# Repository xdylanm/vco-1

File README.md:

# vco-1
Sawtooth core VCO based on Moritz Klein's DIY VCO. 

The general design and test description can be found on Moritz Klein's channel. The oscillator core is a ramp generator driven by a Schmitt trigger inverter and capacitor, controlled by an NPN. 

## Notes

* Using 2N3904 (NPN) and 2N3906 (PNP)
* Implemented a different triangle wave generator based on a precision rectifier circuit. The triangle generator sums a buffered ramp and an inverted, rectified ramp with balancing incorporated with a trimmer on the rectifier sum input.
* Made the coarse adjust an internal trimmer: "factory" tuning involves adjusting the coarse bias on the PNP base with both the coarse level adjust (high side) and divider scaling (low side). Might as well get that set on the bench then fine tune in operation.
* Option to configure the pulse output as a non-inverting summer (from Synth Mages) rather than open loop comparator.
* There are other variants without the Schmitt trigger inverter (e.g. hyestersis in another op-amp). There is also a 12V tolerant single Schmitt trigger inverter (TC4S584F) as an option for a future SMT version. 

## Oscillator Core Theory of Operation

The core of the oscillator is composed of the capacitor C1 and NPN BJT Q1. C1 is charged by the Schmitt trigger inverter U1A through D1 and discharged by Q1. Adjusting the bias on the base of Q1 adjusts the discharge rate of C1. 

The hysteresis on the CD40106 inverter is approximately 3V for a 12V supply (measured 2.8V on the bench). Assuming tuning over six octaves from 16Hz (~$C_0$ ) to 1024Hz (~$C_6$), the discharge time should range from approximately 1ms to 100ms. Using a 2.2nF capacitor for C1, the range of collector currents in Q1 is
$$
I_C \sim C\frac{dV}{dt} \to \left\{\begin{array}{ll}66nA & t_{discharge}=100ms \\ 6.6\mu A & t_{discharge}=1ms\end{array}\right.
$$
The basic model for the collector current is
$$
I_C = I_S \left(e^{\frac{V_{BE}}{V_T}} - 1\right)\to V_{BE}=V_T \ln\left(\frac{I_C}{I_S}+1\right)\simeq V_T(\ln I_C-\ln I_S)
$$
Assuming $I_S=10^{-13}A$, $V_{BE}$ ranges from 350mV to 470mV  ($V_T=26mV$). For larger $I_S$ , the low end of the range for $V_{BE}$ will be reduced (e.g. 290mV for $I_S=10^{-12}A$ ). The span of the range remains constant.

PNP BJT Q2 acts as a buffer in an emitter-follower configuration and counteracts the thermal response of Q1. Since the base voltage of Q1 should be below saturation (approximately 0.4V), there is an 11V drop across R1, which results in a bias current of approximately $11\mu A$ into the emitter and $V_{EB}\sim 0.5V$ for Q2. 

The  CV input is designed for a range between 0 and 5V (V/oct). $V_{BE}$ should vary by 90-120mV, which corresponds to a scaling of 0.018 to 0.024. The resistor divider formed by R6+TH1 and R5+RV1 creates this scaling: R6+TH1 is 110k such that R5+RV1 should range between 2k and 2.6k (R5=1.5k and RV1 ranges from 0 to 2k).

**Tuning Note:** Use an input that varies by 1V (e.g. alternate between 1V and 2V). If the difference in frequency between the same note in adjacent octaves is less than a factor of 2, increase RV1 to increase the gain of the resistor divider.

To set the low end of the range, the network including R19, R20, and RV3 is used to set a bias voltage. This is summed with the CV input through R7+TH3. As with the CV input, R7+TH3 creates a resistor divider with R5+RV1, which determines the gain applied to the bias voltage. Since $V_{EB}$ of Q2 is $\sim 0.5V$ and the low end of the range for $V_B$ of Q1 is 250-350mV, the base of Q2 is biased between -250mV and -150mV (more range here is better depending on the transistor characteristics - the tradeoff is tuning sensitivity). A factor of 40 reduces -12V to -300mV. R19 will limit the low end of the range and R20 will limit the high end. 

**Ideal Tuning**

* Assume $f_{C_0}=16Hz$ is the low frequency reference such that $t_{discharge,0} = 62.5ms$. 

* Use $\Delta V$ from the inverter hysteresis ($\Delta V = 3V$) and C1=2.2nF to obtain 
  $$
  I_{C,0} = C \frac{dV}{dt} = C \Delta V f_{C_0} = 2.2\cdot 10^{-9} \cdot 3 \cdot 16 = 106\mathrm{nA}
  $$

* Determine $V_{BE,0}$ and $\Delta V_{BE}$ , where $V_{BE}$ is the bias voltage to establish current $I_{C,0}$ through the NPN and $\Delta V_{BE}$ is the change in $V_{BE}$ to double the current,  
  $$
  \begin{align*}
  \Delta V_{BE} &\equiv nV_T \ln 2I_{C} - nV_T\ln I_C = nV_T \ln 2 \\
  V_{BE,0} &\equiv nV_T\left(\ln I_{C,0} - \ln I_{S}\right)
  \end{align*}
  $$

* Adjust the gain of the voltage divider (RV1) such that a change of 1V results in a doubling of the current $I_C$ (set $\Delta V_{BE} \approx 18\mathrm{mV}$).

* Adjust the offset with the coarse tuning pot such that the base of the NPN is biased to $V_{BE,0}$ when the input CV is 0V. 

## Assembly and Test

### 1. Power

* Populate the power input and filtering components at the bus connector. Verify the orientation of the polarity protection diodes D2 and D3.
* Connect the board to power and verify voltage levels.

### 2. Oscillator Core, Saw and Pulse Outputs

* Populate the input network (coarse adjust, fine adjust, CV and FM). Note that the board-edge pots (RV2 and RV6) must have their leads trimmed flush with the bottom of the board so that the mono jacks mount flush. Install the pots first and jacks later.
* Populate the transistors Q1 and Q2, socket and 40106 inverter (U1), diode D1 and capacitor C1.
* Populate the socket and TL074 op amp (U2) and the components for the pulse and saw outputs. This is required to generated a buffered signal from the oscillator core at TP9 (or after the DC block at TP3)
* Tune the oscillator (16Hz for a 0V input on CV, 32Hz for 1V, etc.) by adjusting RV1 and RV3. RV1 sets the gain of the voltage divider and should be adjust such that a 1V difference results in a frequency doubling. Next, adjust RV3 to set the base frequency. There is some coupling between the resistive networks, so iteration is required.
* Check the levels for the Saw and Pulse outputs (confirm ~10Vpp). Check the PWM adjustment and confirm a full range of pulse widths.

### 3. Triangle Output

* Populate the discrete components (watch the orientation on diodes D4 and D5) and the socket and TL074 op amp (U3). Populate the last jack.
* Power on the board and check the Triangle output. Adjust RV7 to balance the triangle (it won't be perfect at all frequencies; there is a short spike at the transition).

## Changes

#### V1.1.20240726

* Added additional test points, fixed test point pad to fit standard 0.1" header pins
* R14 to 82k (not tested; pulse out Vpp measured at 8.5V with 68k)
* Added C13 to remove spike in saw output
* R26 to 68k to fix level for triangle output range (now 9.6Vpp)

#### V1.0.20240714

Original PCB

## References

1. Moritz Klein: [DIY VCO Series](https://youtube.com/playlist?list=PLHeL0JWdJLvTuGCyC3qvx0RM39YvopVQN&si=mLFLNtdBjMHdq1OI)
2. Precision rectifier circuit: [Circuit Digest](https://circuitdigest.com/electronic-circuits/half-wave-and-full-wave-precision-rectifier-circuit-using-op-amp)
3. Synth Mages: [DIY VCO variant](https://gitea.circuitlocution.com/synth_mages/MK_VCO)

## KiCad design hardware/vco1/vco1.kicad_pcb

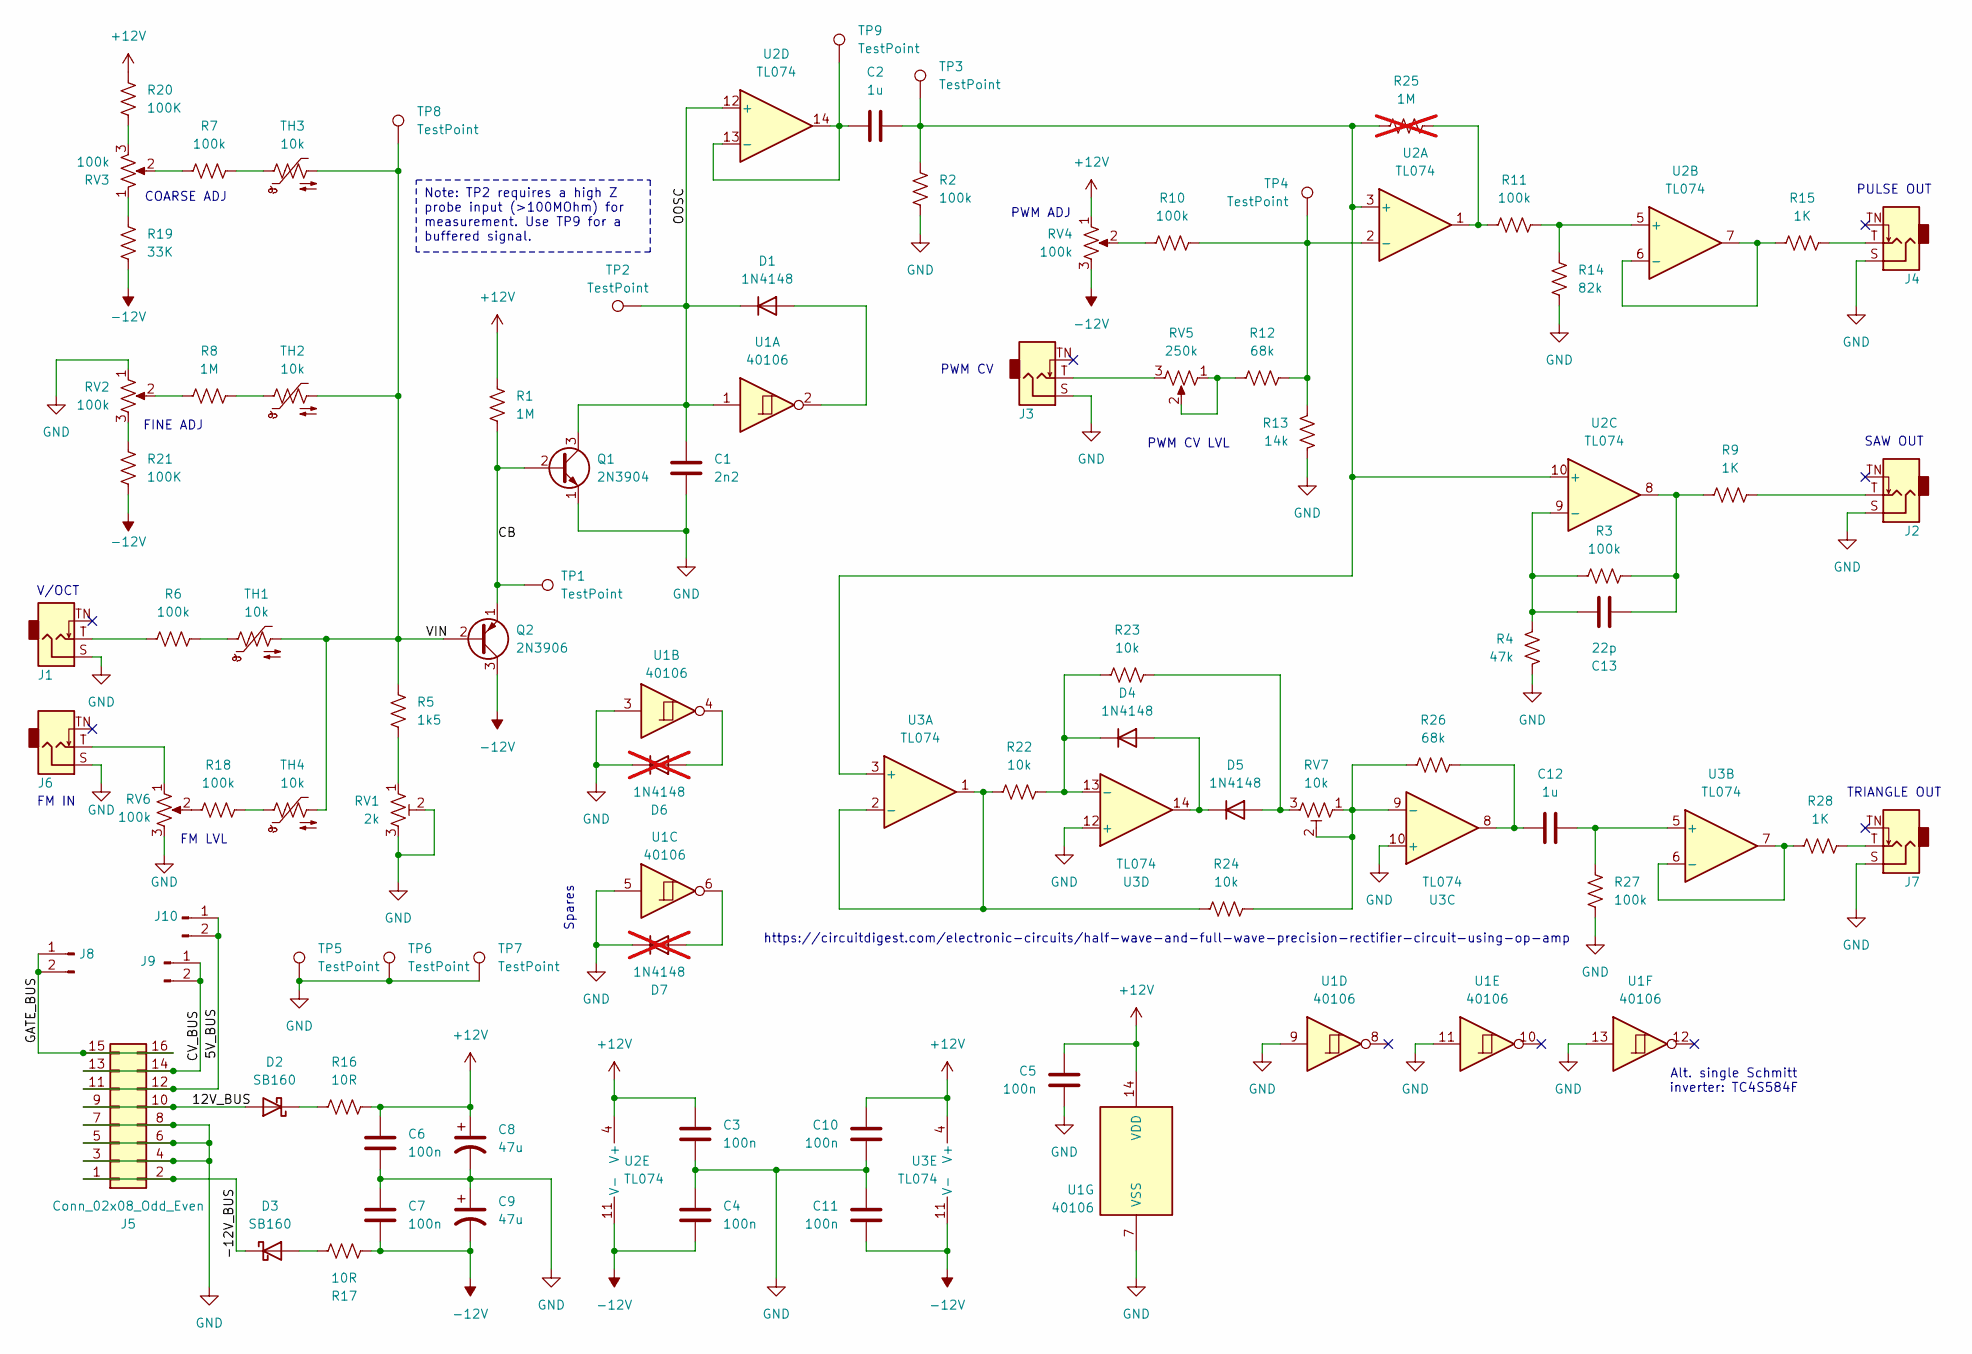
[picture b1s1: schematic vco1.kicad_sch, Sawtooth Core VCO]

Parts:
C1: 2n2; C_Rect_L7.2mm_W2.5mm_P5.00mm_FKS2_FKP2_MKS2_MKP2
C2, C12: 1u; C_Disc_D5.0mm_W2.5mm_P5.00mm
C3, C4, C5, C6, C7, C10, C11: 100n; C_Disc_D5.0mm_W2.5mm_P5.00mm
C8, C9: 47u; CP_Radial_D5.0mm_P2.50mm
C13: 22p; C_Disc_D5.0mm_W2.5mm_P5.00mm
D1, D4, D5: 1N4148; D_DO-35_SOD27_P2.54mm_Vertical_KathodeUp
D2, D3: SB160; D_DO-41_SOD81_P10.16mm_Horizontal
D6, D7: 1N4148; D_DO-35_SOD27_P2.54mm_Vertical_KathodeUp; not fitted
J1, J2, J3, J4, J6, J7: AudioJack2_SwitchT; CONN_MJ-3502
J5: Conn_02x08_Odd_Even; IDC-Header_2x08_P2.54mm_Vertical
J8, J9, J10: Conn_01x02_Pin; PinHeader_1x02_P2.54mm_Vertical
Q1: 2N3904; TO-92_Inline_Wide
Q2: 2N3906; TO-92_Inline_Wide
R1: 1M; R_Axial_DIN0207_L6.3mm_D2.5mm_P7.62mm_Horizontal
R2, R3, R6, R7, R10, R18, R27: 100k; R_Axial_DIN0204_L3.6mm_D1.6mm_P2.54mm_Vertical
R4: 47k; R_Axial_DIN0204_L3.6mm_D1.6mm_P2.54mm_Vertical
R5: 1k5; R_Axial_DIN0204_L3.6mm_D1.6mm_P2.54mm_Vertical
R8: 1M; R_Axial_DIN0204_L3.6mm_D1.6mm_P2.54mm_Vertical
R9: 1K; R_Axial_DIN0207_L6.3mm_D2.5mm_P7.62mm_Horizontal
R11: 100k; R_Axial_DIN0207_L6.3mm_D2.5mm_P10.16mm_Horizontal
R12, R26: 68k; R_Axial_DIN0204_L3.6mm_D1.6mm_P2.54mm_Vertical
R13: 14k; R_Axial_DIN0204_L3.6mm_D1.6mm_P2.54mm_Vertical
R14: 82k; R_Axial_DIN0204_L3.6mm_D1.6mm_P2.54mm_Vertical
R15, R28: 1K; R_Axial_DIN0204_L3.6mm_D1.6mm_P2.54mm_Vertical
R16, R17: 10R; R_Axial_DIN0207_L6.3mm_D2.5mm_P7.62mm_Horizontal
R19: 33K; R_Axial_DIN0204_L3.6mm_D1.6mm_P2.54mm_Vertical
R20, R21: 100K; R_Axial_DIN0204_L3.6mm_D1.6mm_P2.54mm_Vertical
R22, R23, R24: 10k; R_Axial_DIN0204_L3.6mm_D1.6mm_P2.54mm_Vertical
R25: 1M; R_Axial_DIN0207_L6.3mm_D2.5mm_P7.62mm_Horizontal; not fitted
RV1: 2k; Potentiometer_Bourns_3296W_Vertical
RV2, RV4, RV6: 100k; Potentiometer_Bourns_PTV09A-2_Single_Horizontal_3D
RV3: 100k; Potentiometer_Piher_PT-6-V_Vertical
RV5: 250k; Potentiometer_Bourns_PTV09A-2_Single_Horizontal_3D
RV7: 10k; Potentiometer_Piher_PT-6-V_Vertical
TH1, TH2, TH3, TH4: 10k; R_Axial_DIN0207_L6.3mm_D2.5mm_P2.54mm_Vertical
TP1, TP2, TP3, TP4, TP5, TP6, TP7, TP8, TP9: TestPoint; PinHeader_1x01_P2.54mm_Vertical
U1: 40106; DIP-14_W7.62mm_Socket
U2, U3: TL074; DIP-14_W7.62mm_Socket

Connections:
+12V: C3.1, C5.1, C6.1, C8.1, C10.1, R1.1, R16.2, R20.1, RV4.1, U1.14 (VDD), U2.4 (V+), U3.4 (V+)
-12V: C4.2, C7.2, C9.2, C11.2, Q2.3 (C), R17.1, R19.1, R21.2, RV4.3, U2.11 (V-), U3.11 (V-)
/5V_BUS: J5.11, J5.12, J10.1, J10.2
/12V_BUS: D2.2 (A), J5.9, J5.10
/-12V_BUS: D3.1 (K), J5.1, J5.2
/CB: Q1.2 (B), Q2.1 (E), R1.2, TP1.1
/CV_BUS: J5.13, J5.14, J9.1, J9.2
/GATE_BUS: J5.15, J5.16, J8.1, J8.2
/OOSC: C1.1, D1.1 (K), Q1.3 (C), TP2.1, U1.1, U2.12 (+)
/VIN: Q2.2 (B), R5.1, TH1.2, TH2.2, TH3.2, TH4.2, TP8.1
GND: C1.2, C3.2, C4.1, C5.2, C6.2, C7.1, C8.2, C9.1, C10.2, C11.1, D6.1 (K), D7.1 (K), J1.S, J2.S, J3.S, J4.S, J5.3, J5.4, J5.5, J5.6, J5.7, J5.8, J6.S, J7.S, Q1.1 (E), R2.2, R4.1, R13.1, R14.1, R27.2, RV1.2, RV1.3, RV2.1, RV6.3, TP5.1, TP6.1, TP7.1, U1.3, U1.5, U1.7 (VSS), U1.9, U1.11, U1.13, U3.10 (+), U3.12 (+)
unnamed: C12.1, R26.1, U3.8
unnamed: C13.2, R3.2, R9.1, U2.8
unnamed: D1.2 (A), U1.2
unnamed: D2.1 (K), R16.1
unnamed: D3.2 (A), R17.2
unnamed: D4.2 (A), D5.1 (K), U3.14
unnamed: D4.1 (K), R22.1, R23.2, U3.13 (-)
unnamed: D5.2 (A), R23.1, RV7.3
unnamed: D6.2 (A), U1.4
unnamed: D7.2 (A), U1.6
unnamed: J1.T, R6.1
unnamed: J2.T, R9.2
unnamed: J3.T, RV5.3
unnamed: J4.T, R15.2
unnamed: J6.T, RV6.1
unnamed: J7.T, R28.2
unnamed: R5.2, RV1.1
unnamed: R6.2, TH1.1
unnamed: R7.1, RV3.2
unnamed: R7.2, TH3.1
unnamed: R8.1, RV2.2
unnamed: R8.2, TH2.1
unnamed: R10.1, RV4.2
unnamed: R11.1, R25.2, U2.1
unnamed: R12.1, RV5.1, RV5.2
unnamed: R18.1, RV6.2
unnamed: R18.2, TH4.1
unnamed: R19.2, RV3.1
unnamed: R20.2, RV3.3
unnamed: R21.1, RV2.3
unnamed: C2.2, R2.1, R25.1, TP3.1, U2.3 (+), U2.10 (+), U3.3 (+)
unnamed: R10.2, R12.2, R13.2, TP4.1, U2.2 (-)
unnamed: R11.2, R14.2, U2.5 (+)
unnamed: R15.1, U2.6 (-), U2.7
unnamed: C13.1, R3.1, R4.2, U2.9 (-)
unnamed: C2.1, TP9.1, U2.13 (-), U2.14
unnamed: R22.2, R24.2, U3.1, U3.2 (-)
unnamed: C12.2, R27.1, U3.5 (+)
unnamed: R28.1, U3.6 (-), U3.7
unnamed: R24.1, R26.2, RV7.1, RV7.2, U3.9 (-)

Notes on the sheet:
Note: TP2 requires a high Z probe input (>100MOhm) for measurement. Use TP9 for a buffered signal.
TRIANGLE OUT
PWM ADJ
FM IN
COARSE ADJ
FINE ADJ
https://circuitdigest.com/electronic-circuits/half-wave-and-full-wave-precision-rectifier-circuit-using-op-amp
PULSE OUT
PWM CV
PWM CV LVL
FM LVL
Alt. single Schmitt inverter: TC4S584F
SAW OUT
Spares
V/OCT

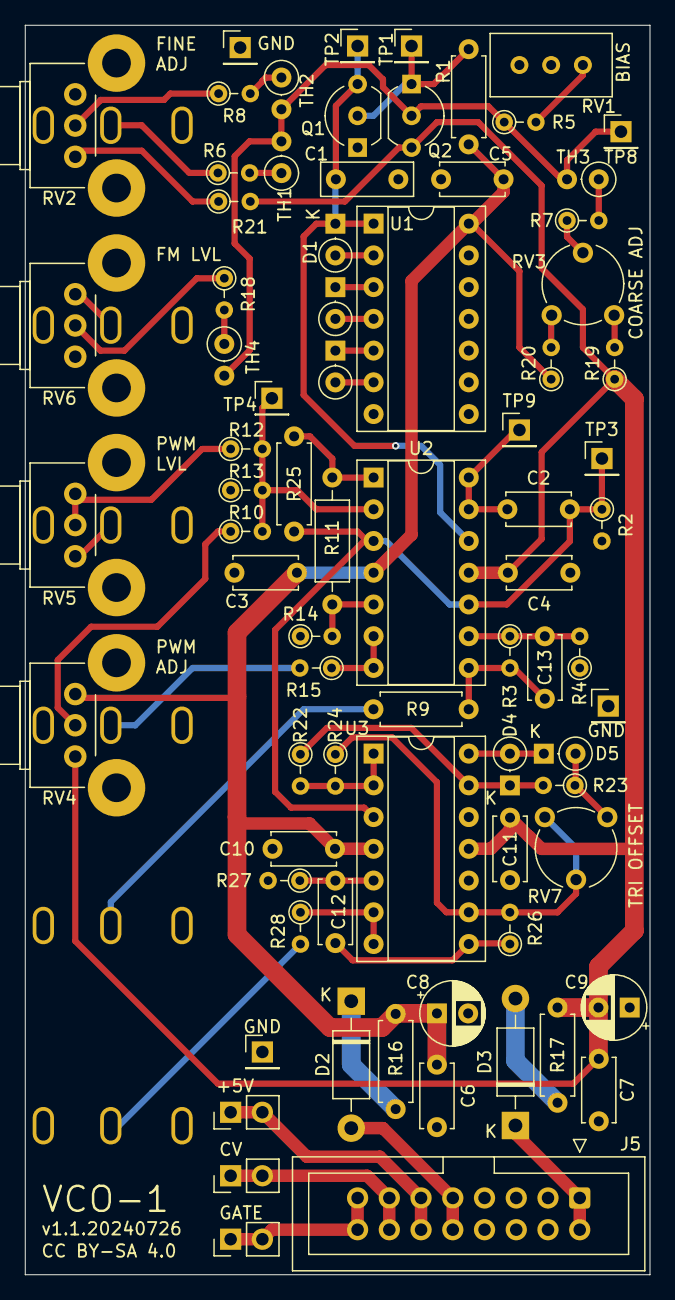
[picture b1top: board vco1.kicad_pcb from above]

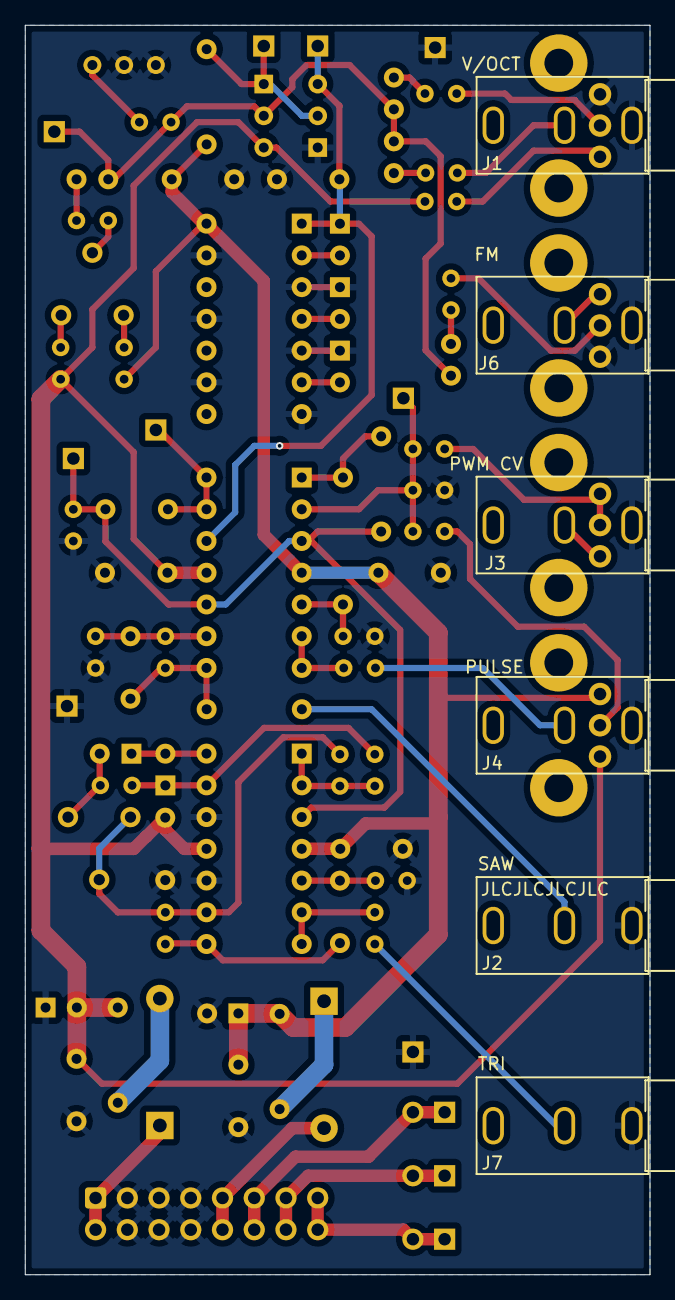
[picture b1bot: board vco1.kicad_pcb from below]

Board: 2 copper layers, 50.0 x 100.0 mm, 83 parts (6 on the bottom side), 51 nets.

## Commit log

2024-07-15 initial board for VCO
2024-07-15 added PDF of schematic & board rendering
2024-07-15 Added a PCB for a front panel (aluminium by JLC)
2024-07-27 added more test points and documentation. Currently cannot adjust to f_osc < 800Hz

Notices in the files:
hardware/vco1/vco1.kicad_pcb:
CC BY-SA 4.0
